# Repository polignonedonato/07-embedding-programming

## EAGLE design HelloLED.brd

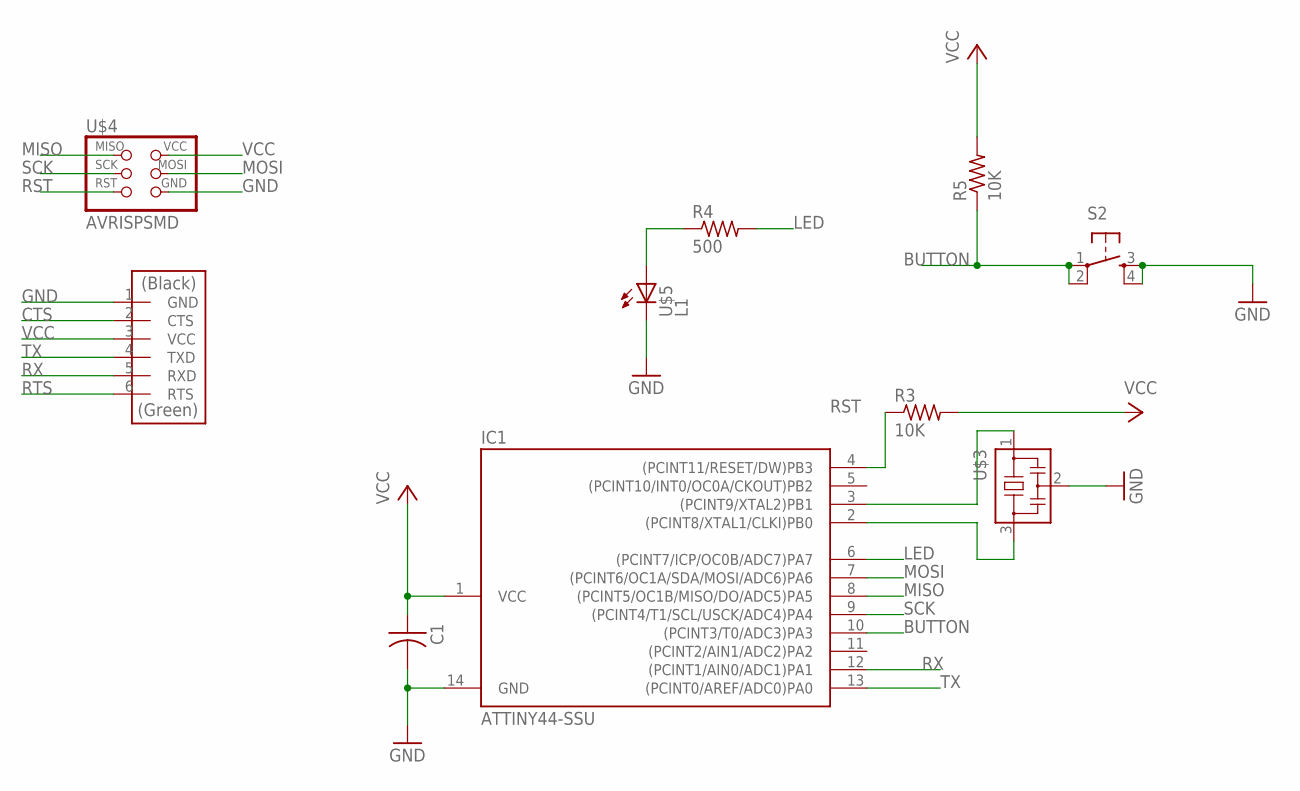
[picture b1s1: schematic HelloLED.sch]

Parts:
C1: CAP-US1206FAB; C1206FAB
IC1: ATTINY44-SSU; SOIC14
R3, R5: 10K; R1206FAB; MPN 12106D226KAT2A
R4: 500; R1206FAB
S2: 6MM_SWITCH6MM_SWITCH; 6MM_SWITCH
U$1: FTDI-SMD-HEADER; 1X06SMD
U$3: RESONATOR; EFOBM
U$4: AVRISPSMD; 2X03SMD
U$5: L1; LED1206FAB

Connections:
BUTTON: IC1.10 ((PCINT3/T0/ADC3)PA3), R5.1, S2.1, S2.2 (P1)
CTS: U$1.2 (CTS)
GND: C1.2, IC1.14 (GND), S2.3 (S), S2.4 (S1), U$1.1 (GND), U$3.2, U$4.6 (GND), U$5.2 (C)
LED: IC1.6 ((PCINT7/ICP/OC0B/ADC7)PA7), R4.2
MISO: IC1.8 ((PCINT5/OC1B/MISO/DO/ADC5)PA5), U$4.1 (MISO)
MOSI: IC1.7 ((PCINT6/OC1A/SDA/MOSI/ADC6)PA6), U$4.4 (MOSI)
unnamed: IC1.2 ((PCINT8/XTAL1/CLKI)PB0), U$3.3
unnamed: IC1.3 ((PCINT9/XTAL2)PB1), U$3.1
unnamed: R4.1, U$5.1 (A)
RST: IC1.4 ((PCINT11/RESET/DW)PB3), R3.1, U$4.5 (RST)
RTS: U$1.6 (RTS)
RX: IC1.12 ((PCINT1/AIN0/ADC1)PA1), U$1.5 (RXD)
SCK: IC1.9 ((PCINT4/T1/SCL/USCK/ADC4)PA4), U$4.3 (SCK)
TX: IC1.13 ((PCINT0/AREF/ADC0)PA0), U$1.4 (TXD)
VCC: C1.1, IC1.1 (VCC), R3.2, R5.2, U$1.3 (VCC), U$4.2 (VCC)

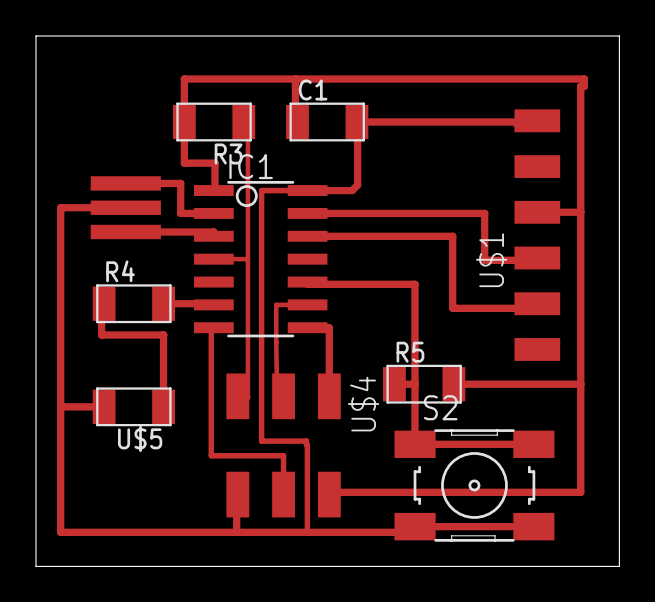
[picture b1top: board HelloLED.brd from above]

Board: 2 copper layers, 32.4 x 29.5 mm, 10 parts (0 on the bottom side), 13 nets.

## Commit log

2016-07-12 embedding programming
    embedding programming
